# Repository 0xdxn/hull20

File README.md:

# HULL/20

A 7 ft flying saucer for a Halloween "spaceport" in a driveway: an octagon of 2020 aluminium extrusion, a clear
24-inch dome with an alien pilot, and **1,406 WS2812B LEDs** on four data lines from an **Arduino Nano ESP32**. Every
few minutes it runs an approach and an abduction; in between it idles like a turbine, with comms, search and power
sputter events. No part of it flashes more than three times a second.

- The build, with photos: https://spaceport.neighb.io/build
- The 2027 refit in 3D: https://spaceport.neighb.io/build/3d (also in `viewer/`, offline)

**No photos are included in this repository.** The images here are drawings, renders and generated previews only.

## What's here

| Folder | What it is | Licence |
|---|---|---|
| `firmware/` | `ufo-show`, the show (Arduino, FastLED), and `ufo-test`, the bench check | MIT |
| `sim/` | The 3D browser sim the show was written in (three.js); the firmware is a line-for-line port of `sim/src/show.js` | MIT (art: CC BY 4.0) |
| `frame/` | The 2020-extrusion frame: drawings, cut sheet, drill/tap guide, assembly steps | CERN-OHL-P-2.0 |
| `cut-files/` | DXFs for the 2027 refit: floating polycarbonate panels and aluminium plates, plus the script that makes them | CERN-OHL-P-2.0 (script: MIT) |
| `viewer/` | Offline 3D viewer of the refit, to scale, assembled or exploded | MIT (three.js: MIT) |
| `pcb/boarding-pass/` | Rev B souvenir boarding pass: a touch switch driving a Darlington pair. KiCad project and fab files | CERN-OHL-P-2.0 |
| `docs/` | The build story, data lines, power, the flash-rate rule, the MQTT contract, wiring drawings | CC BY 4.0 |

Details per path: `LICENSES.md`.

## Build overview

1. **Frame.** 20 bars of 1,220 mm 2020 extrusion, square cuts only, 135° corner brackets, M6 into tapped ends. Start at
   `frame/START-HERE.html`. 87⅛ in across the flats.
2. **LEDs.** Rim 440, dome lip 115 RGBW, spokes 8 x 60, belly disc 241 (nine rings), portholes 8 x 16, eyes 2.
   `docs/DATA-LINES.md` and `docs/wiring/`.
3. **Controller.** Nano ESP32 + 74AHCT125 level shifter + 330 Ω series resistors, on two stacked protoboards.
   `docs/wiring/CONTROLLER-STACK.html`.
4. **Power.** 5 V 60 A supply, one fuse per feed, firmware limit of 30 A. `docs/POWER.md`.
5. **Firmware.** `firmware/README.md`. A fresh clone builds the standalone show with no secrets:
   ```
   arduino-cli compile --fqbn esp32:esp32:nano_nora:PinNumbers=byGPIONumber firmware/ufo-show
   ```
   Wi-Fi + password OTA and MQTT control are opt-in through `firmware/ufo-show/Secrets.h` (copy
   `Secrets.example.h`; it is git-ignored).
6. **Sim.** `cd sim && npm install && npm run build`, then open `sim/index.html`.
7. **2027 refit.** `cut-files/README.md`: the DXFs work with any laser/router shop that takes DXF.

## Bill of materials (summary)

| Part | Qty | Notes |
|---|---|---|
| 2020 aluminium extrusion, 1,220 mm | 20 bars | Cut list in `frame/` and `docs/BUILD.md` |
| 135° 2020 corner brackets | 24 | 3 packs of 8 |
| M6 button/socket screws, stainless; M6 drill-tap bit | | `frame/FRAME-2020.html` has the full hardware list |
| WS2812B strip, 60/m, IP67 | 920 LEDs | 440 rim, 480 spokes |
| SK6812-style RGBW strip, warm white | 115 LEDs | Dome lip |
| 241-LED WS2812B disc, 9 rings | 1 | The belly light |
| 16-LED WS2812B rings | 8 (+2 spare) | Portholes, behind frosted 4 in acrylic discs |
| Aluminium LED channel with milky diffuser, 1 m | 8 | Rim |
| Arduino Nano ESP32 | 1 | |
| 74AHCT125 quad buffer + socket | 1 | 3.3 V to 5 V data |
| 330 Ω resistors | 4 | One per data line |
| Capacitors | | 0.1 µF at the chip, bulk electrolytic at the controller input, 100 µF at each strip start |
| Mean Well LRS-350-5 (5 V, 60 A) | 1 | With inline fuses (15/15/15/10/10/3 A) |
| IP67 enclosure | 1 | Under the deck |
| Clear 24 in dome | 1 | Cockpit |
| Skin | | 2026: aluminised shade cloth. 2027: frosted polycarbonate panels (`cut-files/`) |

## Safety

- **Power.** A 5 V 60 A supply will melt undersized wire long before a household breaker notices. Fuse every feed at
  the supply, size the wire for the fuse, inject power along long runs, and plug into a GFCI outlet. The firmware's
  30 A limiter is a second line of defence, not a substitute for fuses. If you aren't comfortable with the mains side,
  have an electrician wire it. `docs/POWER.md`.
- **Flashing.** The saucer faces a street, so nothing on it flashes faster than **3 times a second** in any area, the
  photosensitive-epilepsy guideline. A flash counter checks the show and every network command stream across 300
  random seeds. If you change the show, re-measure before it goes on the board. `docs/FLASH-RATE.md`.
- **Hanging.** It's 7 ft across. If you hang one, have the structure and rigging checked by someone qualified, use
  rated hardware, and keep people out from under it while it moves.

## Not included

This is the saucer only. The rest of the spaceport stays out of this first release: the LED banner and garage-eyes
firmware, the yard control server and phone app, the Gate 20 passport kiosk, the Planet Hopper passport site and the
neighbourhood site's backend. They depend on private configuration and anti-abuse logic.

## Author

Robb Dixon, 2026.

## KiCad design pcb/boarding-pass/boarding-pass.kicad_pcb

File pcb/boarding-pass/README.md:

# HULL/20 boarding pass, rev B

A souvenir card that is also a working circuit: 89 x 51 mm, 2 layers, 1.0 mm FR-4, black mask, ENIG gold, white
silkscreen. Touch both halves of the gold disc and the beam lights. No battery, no radio, no firmware.

## The circuit

- **USB-C, power only.** CC1/CC2 pulled down with 5.1 kΩ, so any USB-C charger supplies 5 V.
- **The touch switch** is the split gold disc on the front: left half = 5 V, right half = the amplifier's input
  through 100 kΩ.
- **Q1 + Q2 (MMBT3904) as a Darlington pair**, gain about 10,000: the few microamps through a finger, a chain of hands
  or a pencil line switch about 30 mA into three beam LEDs.
- **The beam:** three reverse-mount yellow LEDs (Lite-On LTST-C230KSKT) shine through 1.7 x 2.3 mm cutouts and the
  bare-FR4 beam window, which glows.
- **JP1 "CUT ME":** a bridged solder jumper puts 4.7 MΩ in parallel with the 10 MΩ input pull-down. Cut it and only the
  10 MΩ is left: the input gets twice as touchy (does one half alone now pick up mains hum?).
- **Power star:** one LED behind a star-shaped window, on whenever USB is.
- **Piezo stars (J2):** two LEDs back to back across two pads for a salvaged piezo disc; tap it and a star flashes, no
  USB needed. Not fitted.
- **Spare LED (J3):** two pads with 220 Ω, in parallel with the beam: solder in your own.

Nothing draws current until the disc is closed (the power star aside), so there is no switch. All parts are on the
back, so it assembles one side.

## Files

| Path | What it is |
|---|---|
| `boarding-pass.kicad_pro` / `.kicad_sch` / `.kicad_pcb` / `.kicad_dru` | The KiCad 10 project. Open this to edit. Footprints are embedded in the board |
| `Pass.pretty/` | The custom footprints (project library, `fp-lib-table`) |
| `boarding-pass.ses` | Frozen autorouter session, so a regenerated board gets the same copper |
| `design.py`, `artgen.py`, `rules.kicad_dru` | The generator the board was built from: circuit and placement (`design.py`), every mark of the art as polygons (`artgen.py`). They need a private build toolchain that is **not** part of this release, so treat them as readable source of the design intent; the KiCad files are the editable sources |
| `fab/` | As-ordered manufacturing files: Gerbers + drills (zip), BOM and CPL with LCSC part numbers for PCB assembly, schematic PDF, `SHA256.txt` |
| `renders/` | KiCad 3D renders of the board |

The fab files are the exact set 100 assembled boards were ordered from (October 2026). KiCad DRC on the board: 0
errors, 0 unconnected (KiCad may warn that standard-library footprints and symbols differ from your installed
libraries; those are library-link warnings, not design errors).

The front carries a QR code to the project's public boarding-pass page, `https://spaceport.neighb.io/pass`. Change
`URL` in `artgen.py` (and regenerate) or edit the silkscreen if you make your own.

## Ordering notes

PCB: FR-4, 2 layers, 89 x 51 mm, 1.0 mm, black mask, white silkscreen, ENIG, 1 oz copper, tented vias, no order
number printed on the board. Assembly: bottom side. Not assembled on purpose: J2 (piezo pads), J3 (your-LED pads), JP1
(jumper) and TP1 (the touch disc, which is copper art). Check in the placement preview that each LED's cathode mark
sits on the pad marked K, Q1/Q2 pin 1 matches the silk dot, and the USB-C opening faces the board edge.

Licence: CERN-OHL-P-2.0 (see `../../LICENSES.md`).

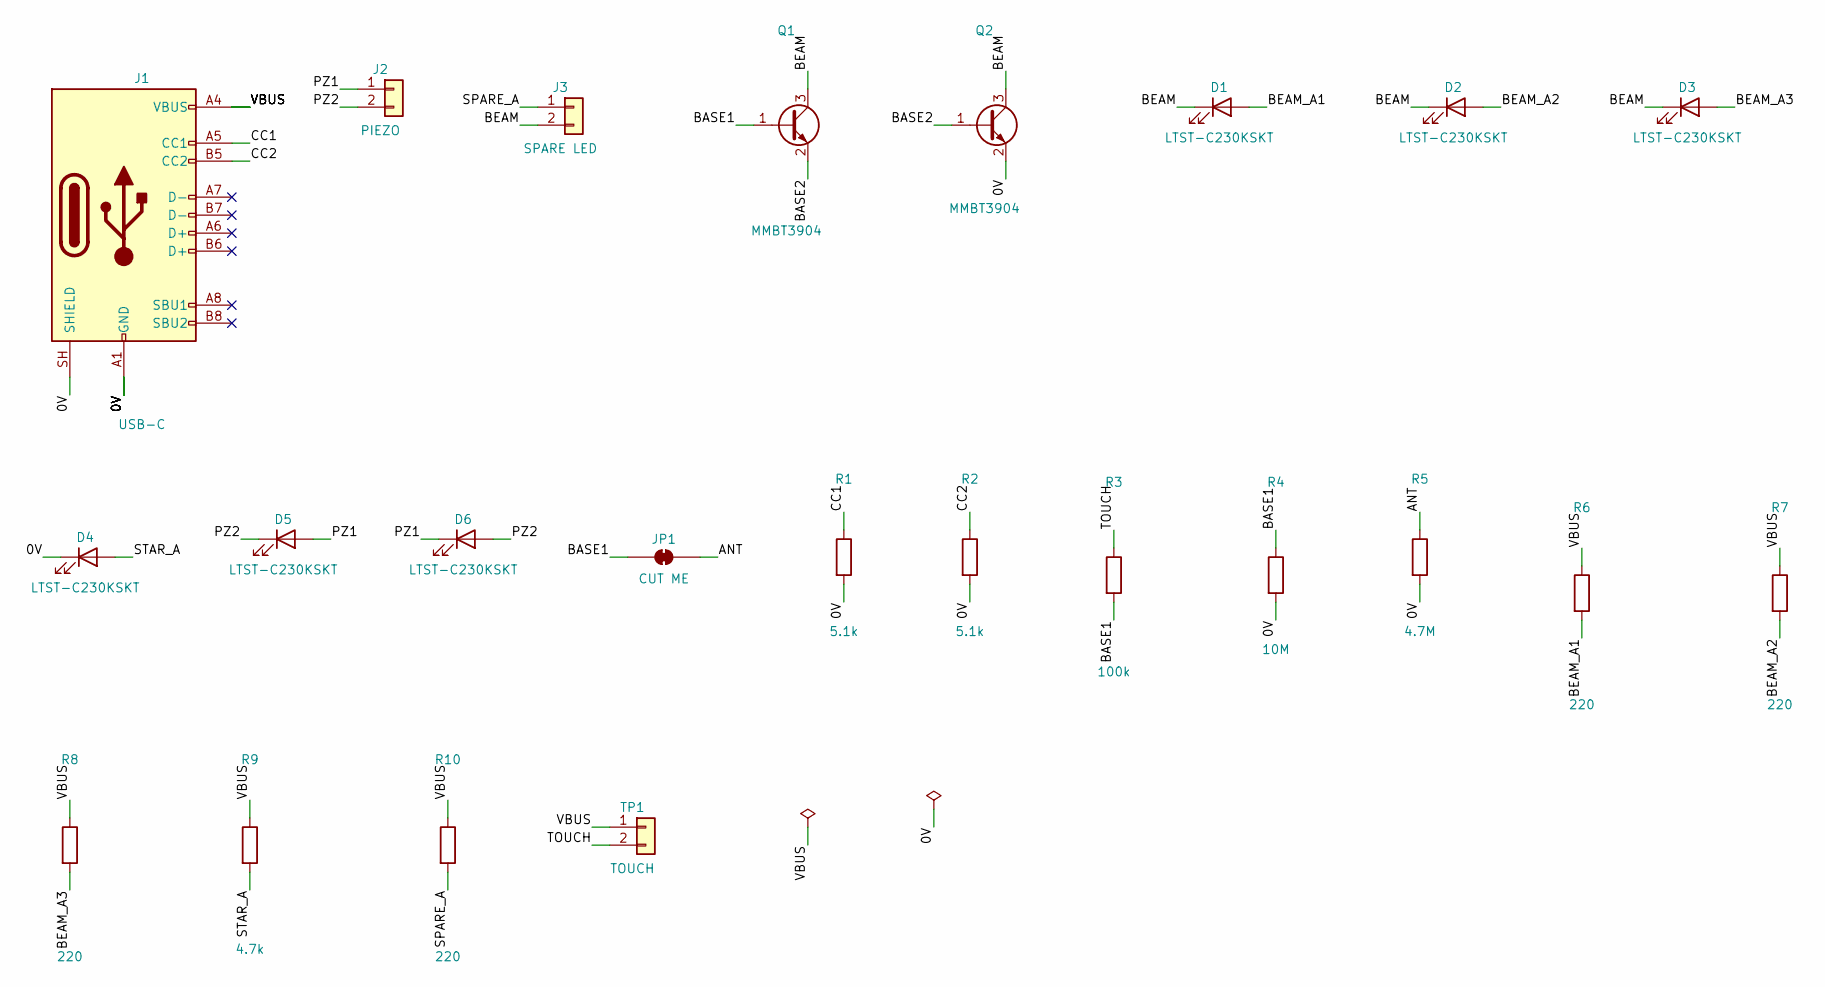
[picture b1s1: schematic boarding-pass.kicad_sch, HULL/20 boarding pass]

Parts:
D1, D2, D3, D4, D5, D6: LTST-C230KSKT; LED_LTST-C230; LCSC C125108
J1: USB-C; USB_C_HRO_TYPE-C-31-M-12_Flush; LCSC C165948
J2: PIEZO; PadPair_3mm
J3: SPARE LED; PadPair_3mm
JP1: CUT ME; SolderJumper-2_P1.3mm_Bridged_RoundedPad1.0x1.5mm
Q1, Q2: MMBT3904; SOT-23; LCSC C20526
R1, R2: 5.1k; R_0603_1608Metric; LCSC C23186
R3: 100k; R_0603_1608Metric; LCSC C25803
R4: 10M; R_0603_1608Metric; LCSC C7250
R5: 4.7M; R_0603_1608Metric; LCSC C177475
R6, R7, R8, R10: 220; R_0603_1608Metric; LCSC C22962
R9: 4.7k; R_0603_1608Metric; LCSC C23162
TP1: TOUCH; TouchSplit

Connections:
0V: D4.1 (K), J1.A1 (GND), J1.A12 (GND), J1.B1 (GND), J1.B12 (GND), J1.SH (SHIELD), Q2.2 (E), R1.2, R2.2, R4.2, R5.2
ANT: JP1.2 (B), R5.1
BASE1: JP1.1 (A), Q1.1 (B), R3.2, R4.1
BASE2: Q1.2 (E), Q2.1 (B)
BEAM: D1.1 (K), D2.1 (K), D3.1 (K), J3.2, Q1.3 (C), Q2.3 (C)
BEAM_A1: D1.2 (A), R6.2
BEAM_A2: D2.2 (A), R7.2
BEAM_A3: D3.2 (A), R8.2
CC1: J1.A5 (CC1), R1.1
CC2: J1.B5 (CC2), R2.1
PZ1: D5.2 (A), D6.1 (K), J2.1
PZ2: D5.1 (K), D6.2 (A), J2.2
SPARE_A: J3.1, R10.2
STAR_A: D4.2 (A), R9.2
TOUCH: R3.1, TP1.2
VBUS: J1.A4 (VBUS), J1.A9 (VBUS), J1.B4 (VBUS), J1.B9 (VBUS), R6.1, R7.1, R8.1, R9.1, R10.1, TP1.1

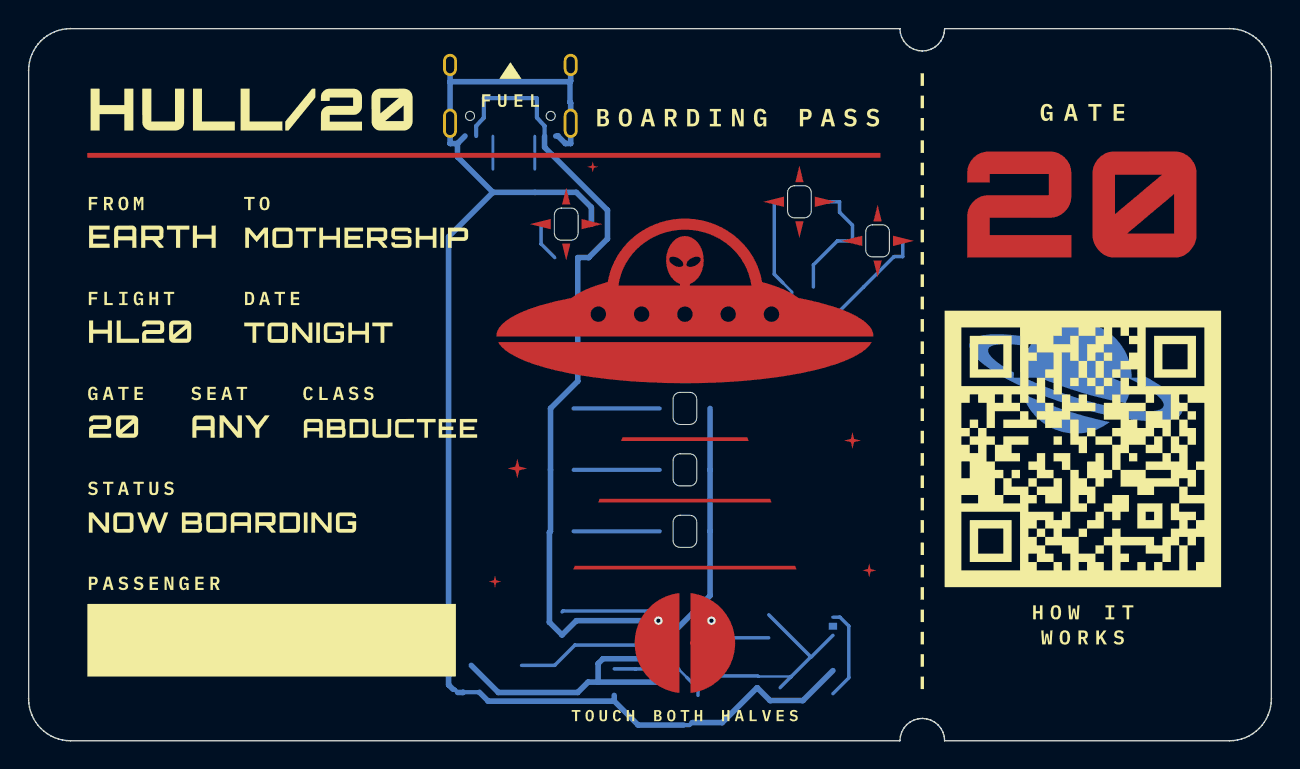
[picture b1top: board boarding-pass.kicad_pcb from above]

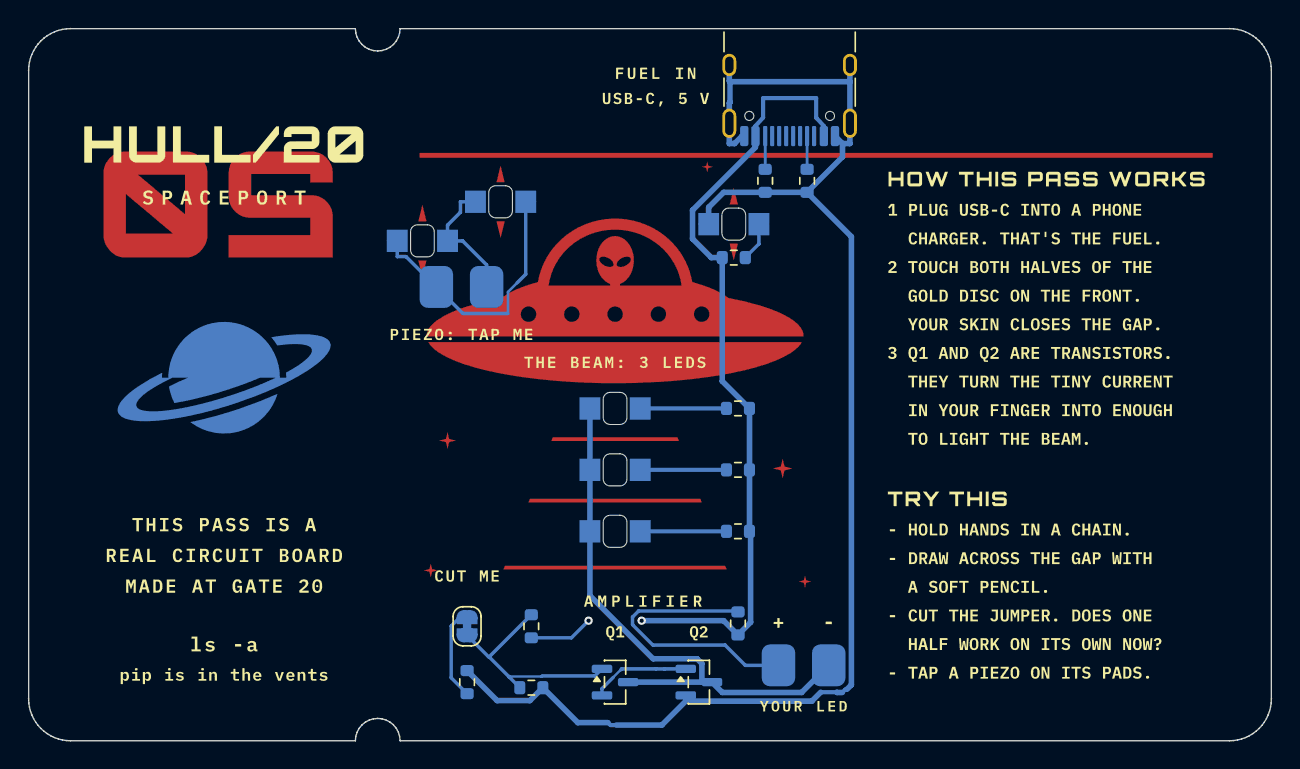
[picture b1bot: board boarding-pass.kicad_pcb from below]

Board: 2 copper layers, 89.0 x 51.0 mm, 23 parts (22 on the bottom side), 16 nets.

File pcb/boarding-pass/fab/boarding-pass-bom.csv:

Comment,Designator,Footprint,LCSC Part #
LTST-C230KSKT,"D1,D2,D3,D4,D5,D6",LED_LTST-C230,C125108
USB-C,J1,USB_C_HRO_TYPE-C-31-M-12_Flush,C165948
MMBT3904,"Q1,Q2",SOT-23,C20526
5.1k,"R1,R2",R_0603_1608Metric,C23186
100k,R3,R_0603_1608Metric,C25803
10M,R4,R_0603_1608Metric,C7250
4.7M,R5,R_0603_1608Metric,C177475
220,"R6,R7,R8,R10",R_0603_1608Metric,C22962
4.7k,R9,R_0603_1608Metric,C23162
